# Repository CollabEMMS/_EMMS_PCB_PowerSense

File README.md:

# _EMMS_PCB_PowerSense

<p> THIS IS NOT THE ACTUAL LATEST VERSION. THE ACTUAL POWER SENSE IS IN "Power Sense 3.0" and should be moved over to this folder </p>

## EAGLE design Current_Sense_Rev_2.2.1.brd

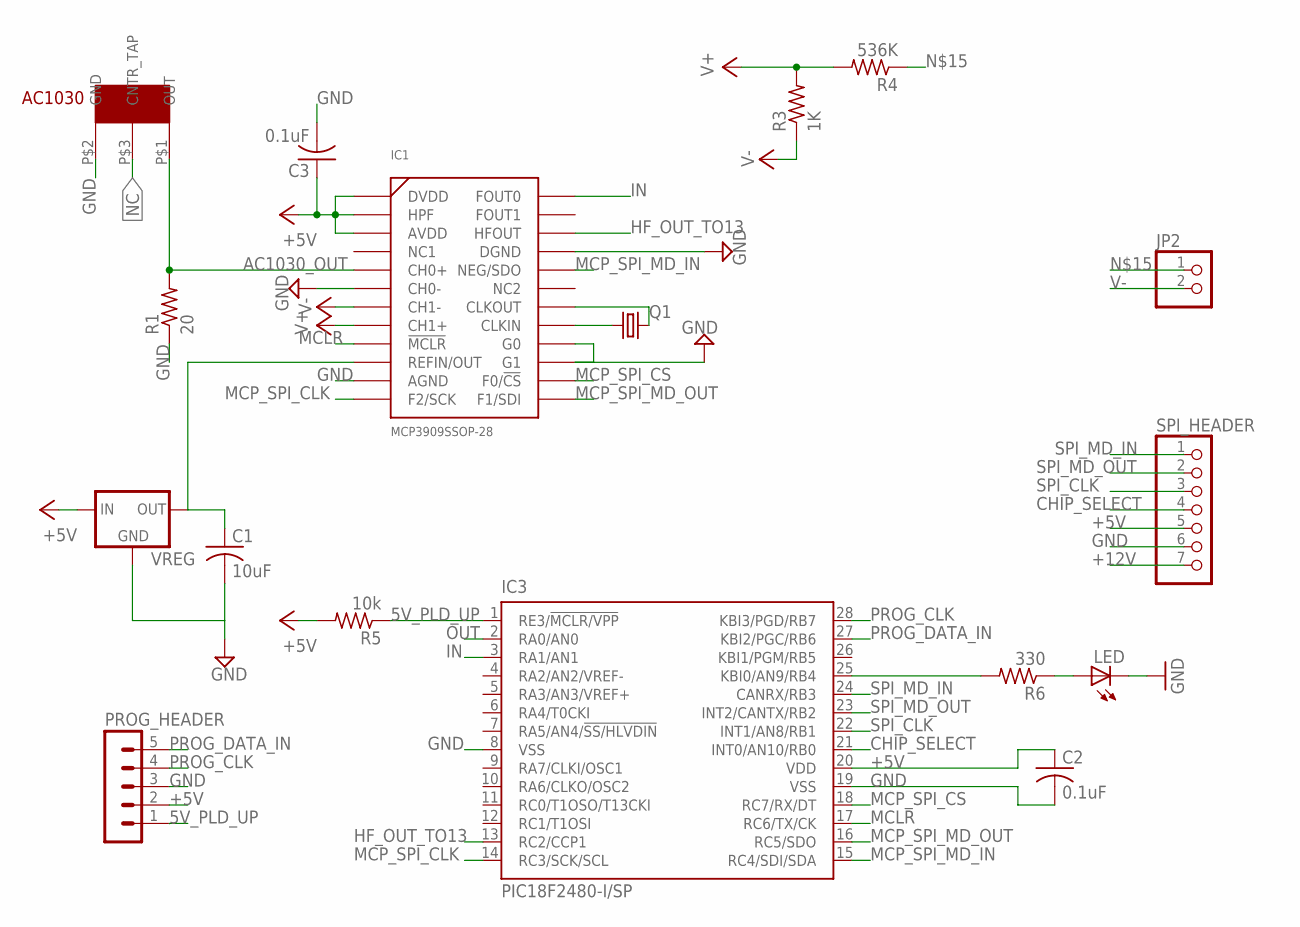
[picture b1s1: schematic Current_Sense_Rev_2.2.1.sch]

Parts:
AC1030: AC1030
C1: 10uF; C025-024X044
C2, C3: 0.1uF; C025-024X044
IC1: MCP3909SSOP-28; SSOP-24
IC3: PIC18F2480-I/SP; DIL28-3
JP2: PINHD-1X2; 1X02
LED: LED3MM
PROG_HEADER: MA05-1
Q1: CRYSTALHC49S; HC49/S
R1: 20; 0204/7
R3: 1K; 0204/7
R4: 536K; 0204/7
R5: 10k; 0204/7
R6: 330; 0204/7
SPI_HEADER: PINHD-1X7; 1X07
VREG: MCP1700INLINE; TO92-INLINE

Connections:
5V_PLD_UP: IC3.1 (RE3/!MCLR/VPP), PROG_HEADER.1, R5.1
+5V: C2.1, C3.1, IC1.1 (DVDD), IC1.2 (HPF), IC1.3 (AVDD), IC3.20 (VDD), PROG_HEADER.2, R5.2, SPI_HEADER.5, VREG.2 (IN)
+12V: SPI_HEADER.7
AC1030_OUT: AC1030.P$1 (OUT), IC1.5 (CH0+), R1.2
CHIP_SELECT: IC3.21 (INT0/AN10/RB0), SPI_HEADER.4
GND: AC1030.P$2 (GND), C1.2, C2.2, C3.2, IC1.6 (CH0-), IC1.11 (AGND), IC1.15 (G1), IC1.16 (G0), IC1.21 (DGND), IC3.8 (VSS), IC3.19 (VSS), LED.K (C), PROG_HEADER.3, R1.1, SPI_HEADER.6, VREG.1 (GND)
HF_OUT_TO13: IC1.22 (HFOUT), IC3.13 (RC2/CCP1)
IN: IC1.24 (FOUT0), IC3.3 (RA1/AN1)
MCLR: IC1.9 (!MCLR!), IC3.17 (RC6/TX/CK)
MCP_SPI_CLK: IC1.12 (F2/SCK), IC3.14 (RC3/SCK/SCL)
MCP_SPI_CS: IC1.14 (F0/!CS!), IC3.18 (RC7/RX/DT)
MCP_SPI_MD_IN: IC1.20 (NEG/SDO), IC3.15 (RC4/SDI/SDA)
MCP_SPI_MD_OUT: IC1.13 (F1/SDI), IC3.16 (RC5/SDO)
unnamed: IC3.25 (KBI0/AN9/RB4), R6.2
unnamed: LED.A, R6.1
unnamed: IC1.17 (CLKIN), Q1.1
unnamed: IC1.18 (CLKOUT), Q1.2
unnamed: C1.1, IC1.10 (REFIN/OUT), VREG.3 (OUT)
unnamed: JP2.1, R4.1
NC: AC1030.P$3 (CNTR_TAP)
OUT: IC3.2 (RA0/AN0)
PROG_CLK: IC3.28 (KBI3/PGD/RB7), PROG_HEADER.4
PROG_DATA_IN: IC3.27 (KBI2/PGC/RB6), PROG_HEADER.5
SPI_CLK: IC3.22 (INT1/AN8/RB1), SPI_HEADER.3
SPI_MD_IN: IC3.24 (CANRX/RB3), SPI_HEADER.1
SPI_MD_OUT: IC3.23 (INT2/CANTX/RB2), SPI_HEADER.2
V+: IC1.8 (CH1+), R3.2, R4.2
V-: IC1.7 (CH1-), JP2.2, R3.1

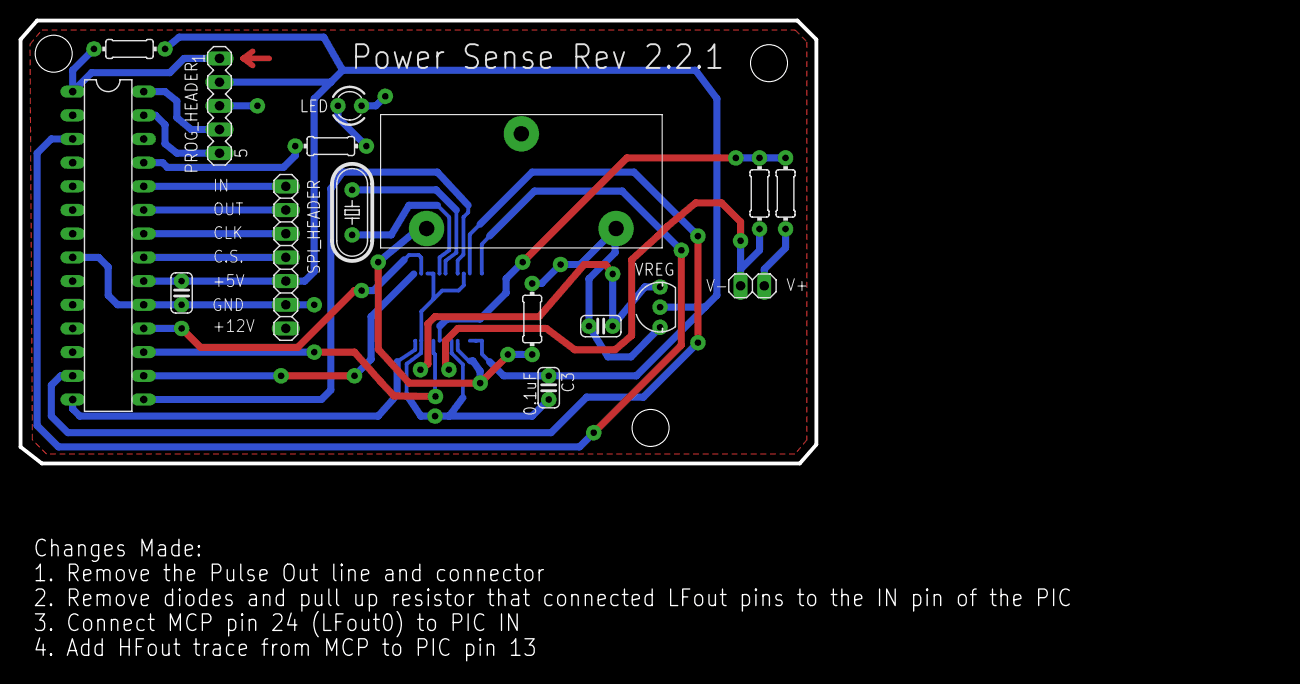
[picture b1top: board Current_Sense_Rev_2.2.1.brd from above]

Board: 2 copper layers, 135.0 x 68.9 mm, 17 parts (1 on the bottom side), 25 nets.

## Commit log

2018-02-06 Initial Files
2018-02-06 Init Files
2018-02-20 Removed 2.2, added 2.3
    Removed version 2.2 so 2.3 could be added
2018-02-20 Version Number, CL, etc
    Corrected Version Number from 2.3 to 2.2.1
    Updated CL
    Fixed changes text layer
2020-02-11 PS3.0 -> The right folder
    Moving things from where they were in the Power Sense 3.0 repository into the actual PCB_PowerSense repository
2021-02-13 Power Sense New Layout
    -- Moved Molex connector slot to match up (Not checked very well) to the command board.
    -- Need to Still double check the mounting holes!
    @Seth let's do a printout again but this time with adopted code
